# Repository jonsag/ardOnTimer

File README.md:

# ardOnTimer
An on timer with relay, mainly for use in an UV exposure box.  

Time is set with buttons and visualized on an LCD display.  

When setting new time it's saved in eeprom and reloaded at startup.  

Timer range is from 10 seconds to 9 hours, 59 minutes and 59 seconds in 10 seconds steps.  
This can be changed in configuration file.  

Parts list
==========
1 x Arduino Uno, kjell.com art#88860  
1 x LCD display 2x16 characters, kjell.com art# 90215  
1 x Relay module KY-019, kjell.com art# 87878  
1 x Buzzer, kjell.com art# 87887  
4 x Switch, kjell.com art# 36011  
1 x 10kohm potentiometer  
4 x 10kohm resistor  
1 x 220ohm resistor  
1x 100ohm resistor  

Screens
==========
The timer has three screens.  
Second row on screens shows which buttons are active.  

Standby screen
----------
Waiting for start or set.  

 * Start/Stop/Store button to start timer and enter run screen.  
 * Set button to enter set screen.  

Run screen
----------
Shows spinning bar and time left on first row, and progressbar on the second.  

 * Start/Stop/Store button to stop timer and go back to standby screen.  

Set screen
----------
Setting timer.  

* Start/Stop/Store button to store set time.  
* Set button to exit back to standby screen. If set time was not stored, previous time will be used.  
* Up or Down button to increase/decrease time. Each press adds/subtracts 10 seconds from time. Long press adds/subtracts one minute from time. Holding down button keeps stepping minutes.

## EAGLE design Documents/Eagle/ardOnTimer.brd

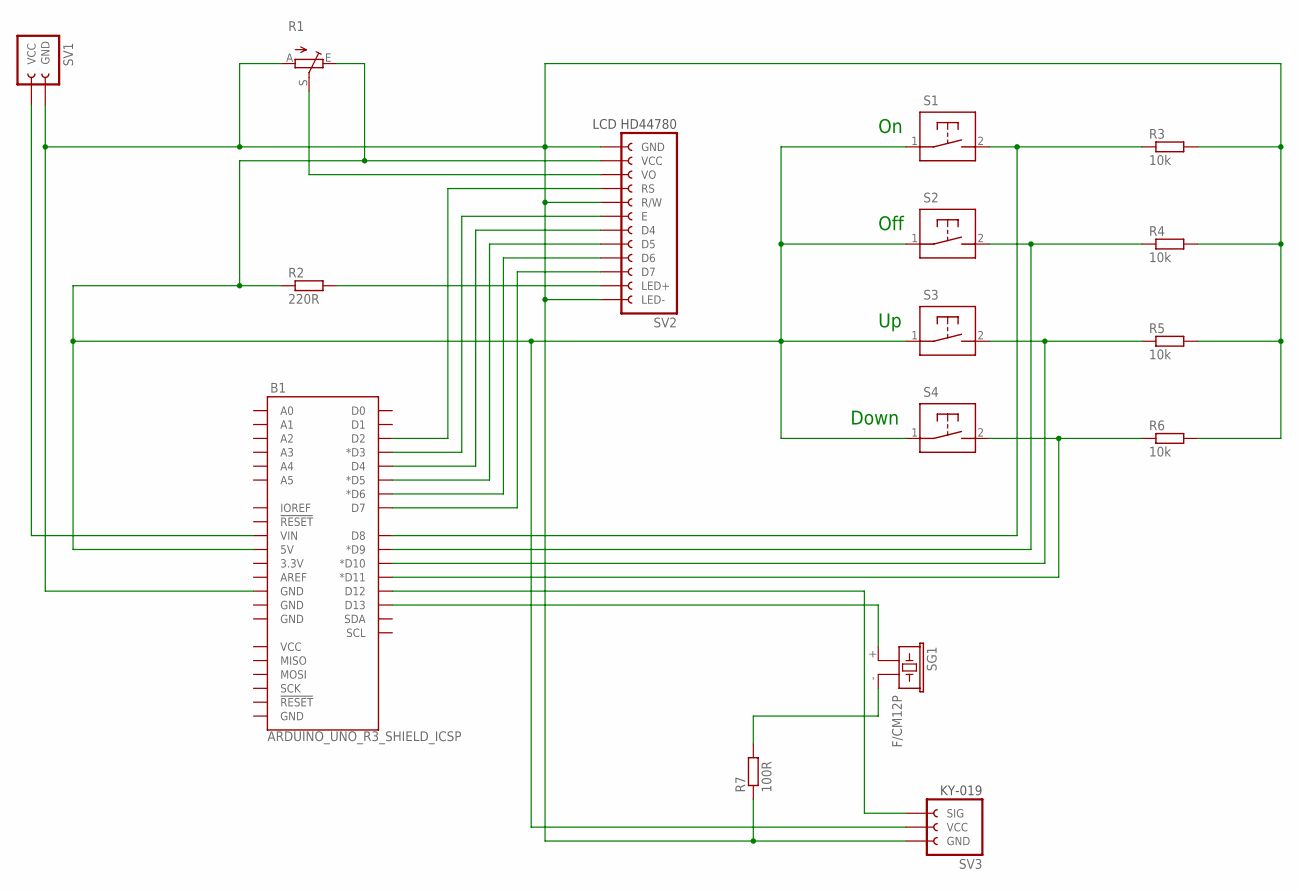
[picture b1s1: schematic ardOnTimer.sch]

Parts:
B1: ARDUINO_UNO_R3_SHIELD_ICSP; UNO_R3_SHIELD_ICSP
R1: POTENTIOMETER_CA6VCA6V; CA6V
R2: 220R; 0204/7
R3, R4, R5, R6: 10k; 0204/7
R7: 100R; 0204/7
S1, S2, S3, S4: NO_SWITCH_2-PIN-FEMALE_HEADER
SG1: F/CM12P
SV1: POWER_IN-2-PIN_FEMALE_HEADER
SV2: LCD-HD44780-12-PIN_FEMALE_HEADER
SV3: KY-019_3-PIN_FEMALE_HEADERANGLED_W_MOUNT_HOLES; KY-019_3-PIN_FEMALE_HEADER_ANGLED_W_MOUNT_HOLES

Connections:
unnamed: B1.GND@2 (GND), R1.A, R3.2, R4.2, R5.2, R6.2, R7.1, SV1.GND, SV2.GND, SV2.LED-, SV2.R/W, SV3.GND
unnamed: B1.D13, SG1.+ (1)
unnamed: R1.S, SV2.VO
unnamed: R2.2, SV2.LED+
unnamed: B1.D2, SV2.RS
unnamed: B1.D3 (*D3), SV2.E
unnamed: B1.D4, SV2.D4
unnamed: B1.D5 (*D5), SV2.D5
unnamed: B1.D6 (*D6), SV2.D6
unnamed: B1.D7, SV2.D7
unnamed: B1.VIN, SV1.VCC
unnamed: B1.5V, R1.E, R2.1, S1.1, S2.1, S3.1, S4.1, SV2.VCC, SV3.VCC
unnamed: B1.D8, R3.1, S1.2 (S)
unnamed: B1.D9 (*D9), R4.1, S2.2 (S)
unnamed: B1.D10 (*D10), R5.1, S3.2 (S)
unnamed: B1.D11 (*D11), R6.1, S4.2 (S)
unnamed: B1.D12, SV3.SIG
unnamed: R7.2, SG1.- (2)

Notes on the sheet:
Off
Down

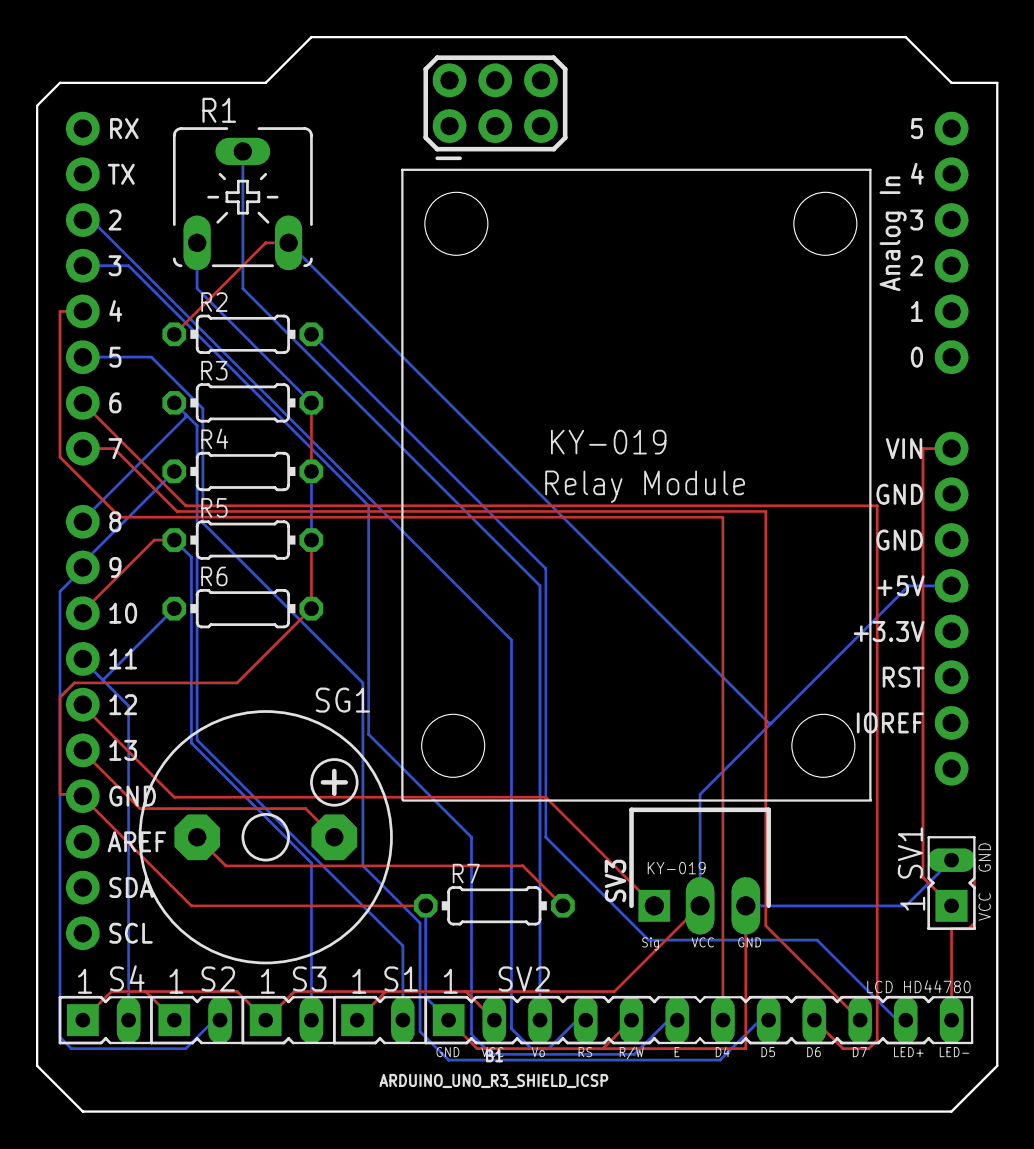
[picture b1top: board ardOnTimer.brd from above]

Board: 2 copper layers, 53.3 x 59.7 mm, 16 parts (0 on the bottom side), 18 nets.

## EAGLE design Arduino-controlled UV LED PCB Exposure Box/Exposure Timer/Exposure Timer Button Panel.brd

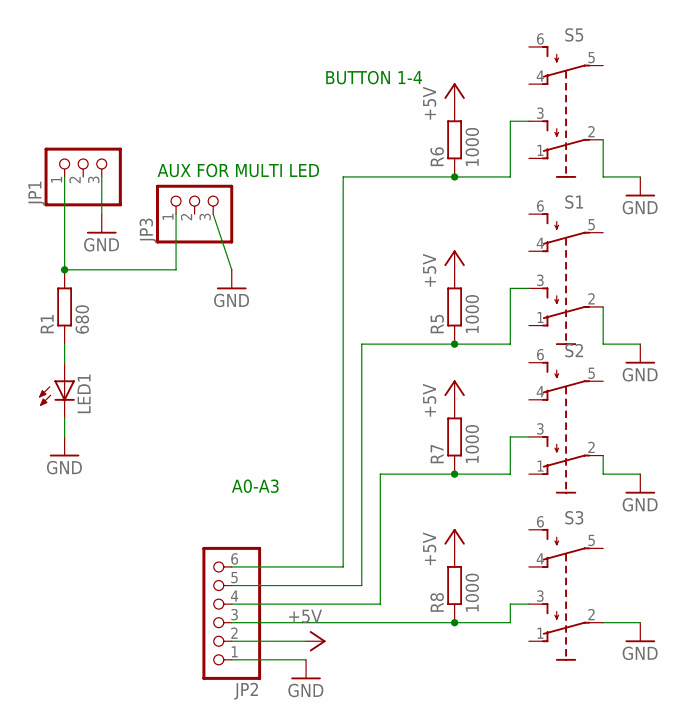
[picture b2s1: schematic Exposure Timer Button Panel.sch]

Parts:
JP1, JP3: PINHD-1X3; 1X03
JP2: PINHD-1X6; 1X06
LED1: LED5MM
R1: 680; 0204/7
R5, R6, R7, R8: 1000; 0204/7
S1, S2, S3, S5: TL42PO; TL4XPO

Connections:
+5V: JP2.2, R5.2, R6.2, R7.2, R8.2
GND: JP1.3, JP2.1, JP3.3, LED1.K (C), S1.2, S2.2, S3.2, S5.2
unnamed: JP1.1, JP3.1, R1.2
unnamed: LED1.A, R1.1
unnamed: JP2.6, R6.1, S5.3 (S)
unnamed: JP2.5, R5.1, S1.3 (S)
unnamed: JP2.4, R7.1, S2.3 (S)
unnamed: JP2.3, R8.1, S3.3 (S)

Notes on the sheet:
BUTTON 1-4
A0-A3
AUX FOR MULTI LED

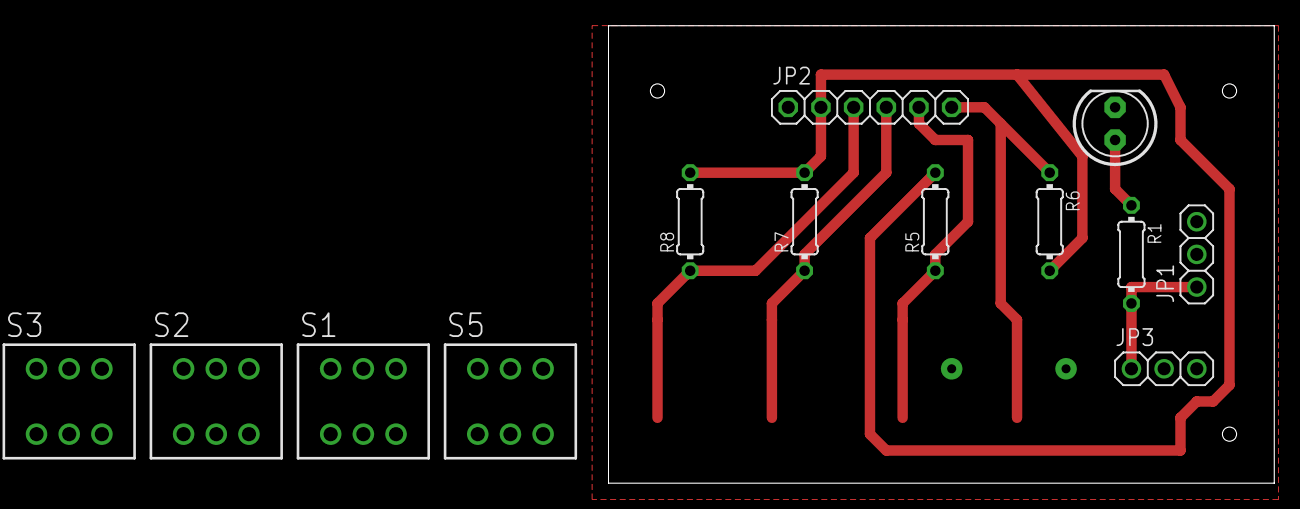
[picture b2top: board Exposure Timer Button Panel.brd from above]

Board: 2 copper layers, 51.7 x 35.5 mm, 13 parts (0 on the bottom side), 8 nets.

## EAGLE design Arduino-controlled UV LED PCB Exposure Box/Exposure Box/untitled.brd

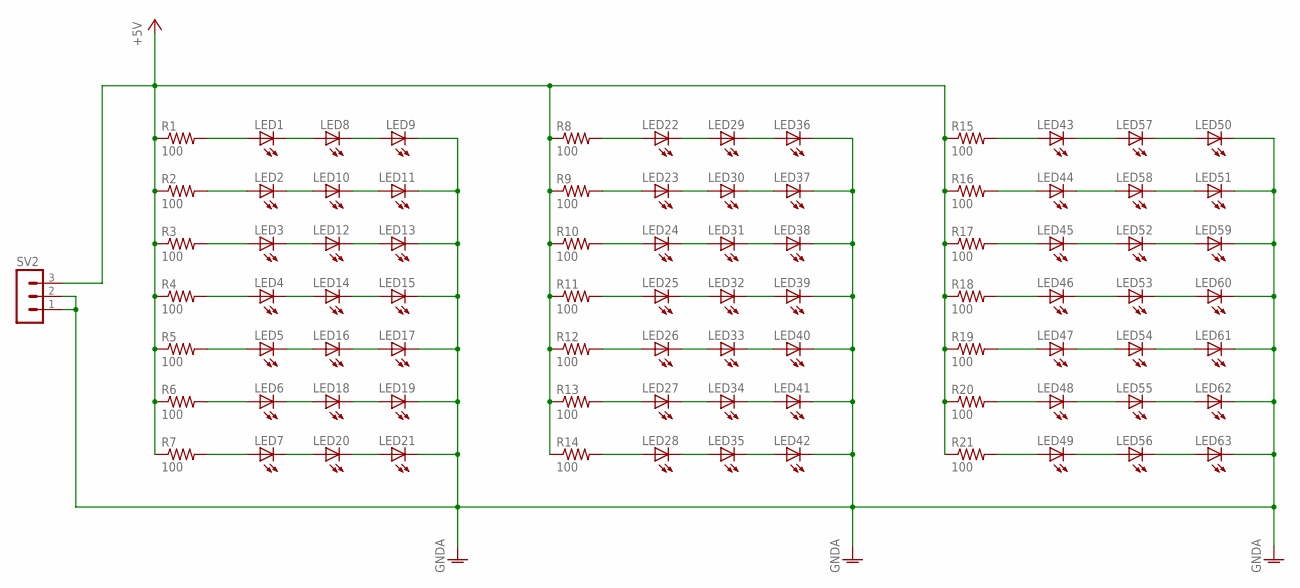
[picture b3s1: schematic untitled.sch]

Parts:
LED1, LED2, LED3, LED4, LED5, LED6, LED7, LED8, LED9, LED10, LED11, LED12, LED13, LED14, LED15, LED16, LED17, LED18, LED19, LED20, LED21, LED22, LED23, LED24, LED25, LED26, LED27, LED28, LED29, LED30, LED31, LED32, LED33, LED34, LED35, LED36, LED37, LED38, LED39, LED40, LED41, LED42, LED43, LED44, LED45, LED46, LED47, LED48, LED49, LED50, LED51, LED52, LED53, LED54, LED55, LED56, LED57, LED58, LED59, LED60, LED61, LED62, LED63: LED5MM
R1, R2, R3, R4, R5, R6, R7, R8, R9, R10, R11, R12, R13, R14, R15, R16, R17, R18, R19, R20, R21: 100; 0204/5
SV2: MA03-1

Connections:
+5V: R1.1, R2.1, R3.1, R4.1, R5.1, R6.1, R7.1, R8.1, R9.1, R10.1, R11.1, R12.1, R13.1, R14.1, R15.1, R16.1, R17.1, R18.1, R19.1, R20.1, R21.1, SV2.3
GNDA: LED9.K (C), LED11.K (C), LED13.K (C), LED15.K (C), LED17.K (C), LED19.K (C), LED21.K (C), LED36.K (C), LED37.K (C), LED38.K (C), LED39.K (C), LED40.K (C), LED41.K (C), LED42.K (C), LED50.K (C), LED51.K (C), LED59.K (C), LED60.K (C), LED61.K (C), LED62.K (C), LED63.K (C), SV2.1, SV2.2
unnamed: LED43.K (C), LED57.A
unnamed: LED52.K (C), LED59.A
unnamed: LED1.A, R1.2
unnamed: LED2.A, R2.2
unnamed: LED3.A, R3.2
unnamed: LED4.A, R4.2
unnamed: LED5.A, R5.2
unnamed: LED6.A, R6.2
unnamed: LED7.A, R7.2
unnamed: LED53.K (C), LED60.A
unnamed: LED1.K (C), LED8.A
unnamed: LED8.K (C), LED9.A
unnamed: LED10.K (C), LED11.A
unnamed: LED2.K (C), LED10.A
unnamed: LED3.K (C), LED12.A
unnamed: LED12.K (C), LED13.A
unnamed: LED54.K (C), LED61.A
unnamed: LED4.K (C), LED14.A
unnamed: LED14.K (C), LED15.A
unnamed: LED16.K (C), LED17.A
unnamed: LED5.K (C), LED16.A
unnamed: LED6.K (C), LED18.A
unnamed: LED18.K (C), LED19.A
unnamed: LED20.K (C), LED21.A
unnamed: LED7.K (C), LED20.A
unnamed: LED55.K (C), LED62.A
unnamed: LED56.K (C), LED63.A
unnamed: LED22.A, R8.2
unnamed: LED23.A, R9.2
unnamed: LED24.A, R10.2
unnamed: LED25.A, R11.2
unnamed: LED26.A, R12.2
unnamed: LED27.A, R13.2
unnamed: LED28.A, R14.2
unnamed: LED22.K (C), LED29.A
unnamed: LED29.K (C), LED36.A
unnamed: LED30.K (C), LED37.A
unnamed: LED23.K (C), LED30.A
unnamed: LED24.K (C), LED31.A
unnamed: LED31.K (C), LED38.A
unnamed: LED32.K (C), LED39.A
unnamed: LED25.K (C), LED32.A
unnamed: LED26.K (C), LED33.A
unnamed: LED27.K (C), LED34.A
unnamed: LED28.K (C), LED35.A
unnamed: LED33.K (C), LED40.A
unnamed: LED34.K (C), LED41.A
unnamed: LED35.K (C), LED42.A
unnamed: LED50.A, LED57.K (C)
unnamed: LED51.A, LED58.K (C)
unnamed: LED44.K (C), LED58.A
unnamed: LED43.A, R15.2
unnamed: LED44.A, R16.2
unnamed: LED45.A, R17.2
unnamed: LED46.A, R18.2
unnamed: LED47.A, R19.2
unnamed: LED48.A, R20.2
unnamed: LED49.A, R21.2
unnamed: LED45.K (C), LED52.A
unnamed: LED46.K (C), LED53.A
unnamed: LED47.K (C), LED54.A
unnamed: LED48.K (C), LED55.A
unnamed: LED49.K (C), LED56.A

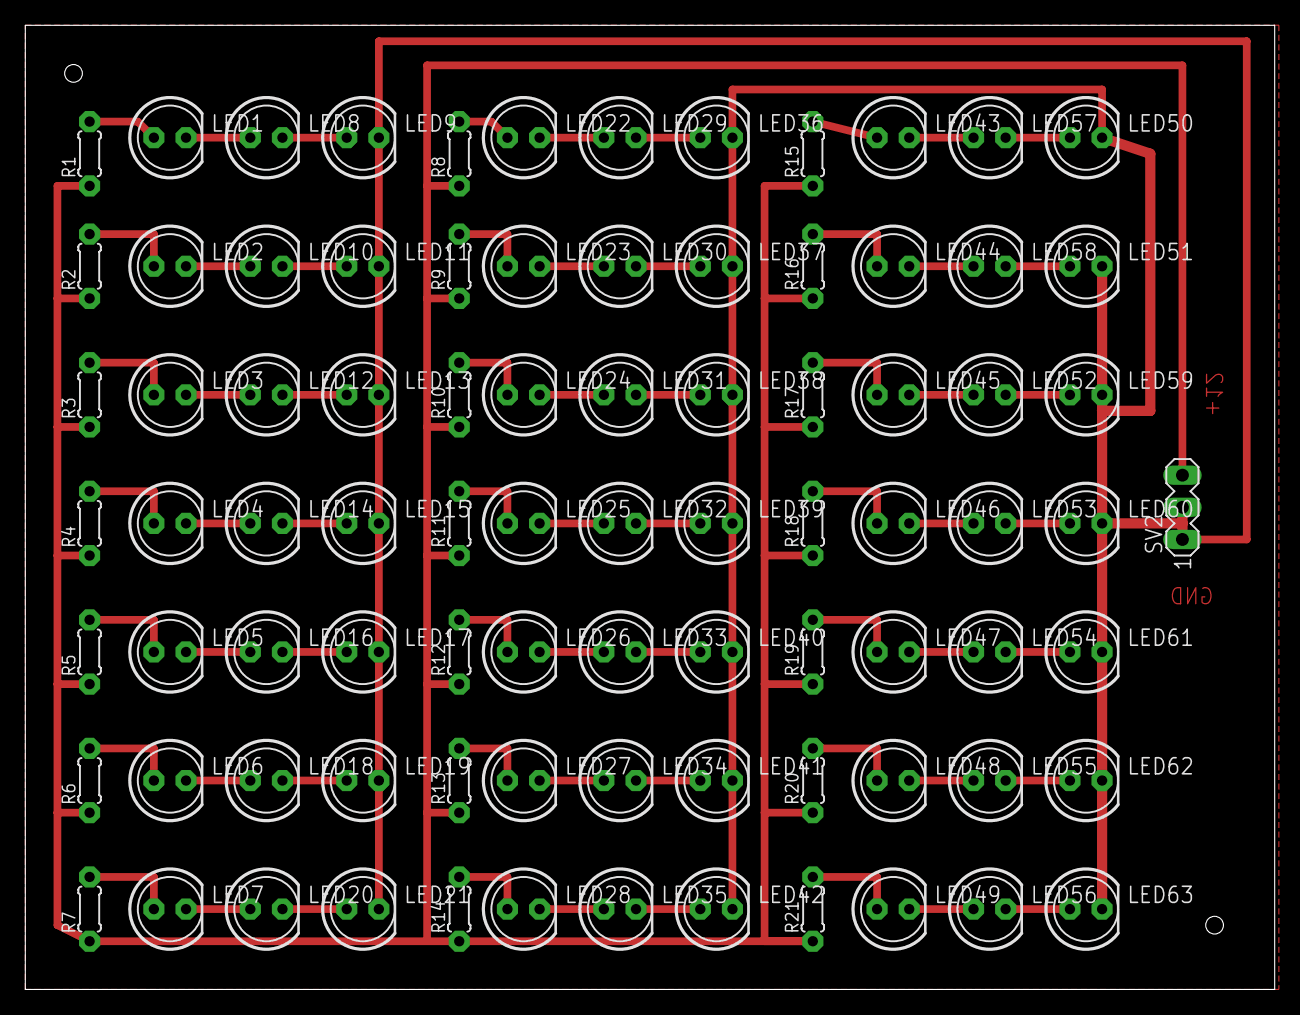
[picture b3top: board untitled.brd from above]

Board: 2 copper layers, 98.7 x 76.2 mm, 85 parts (0 on the bottom side), 65 nets.

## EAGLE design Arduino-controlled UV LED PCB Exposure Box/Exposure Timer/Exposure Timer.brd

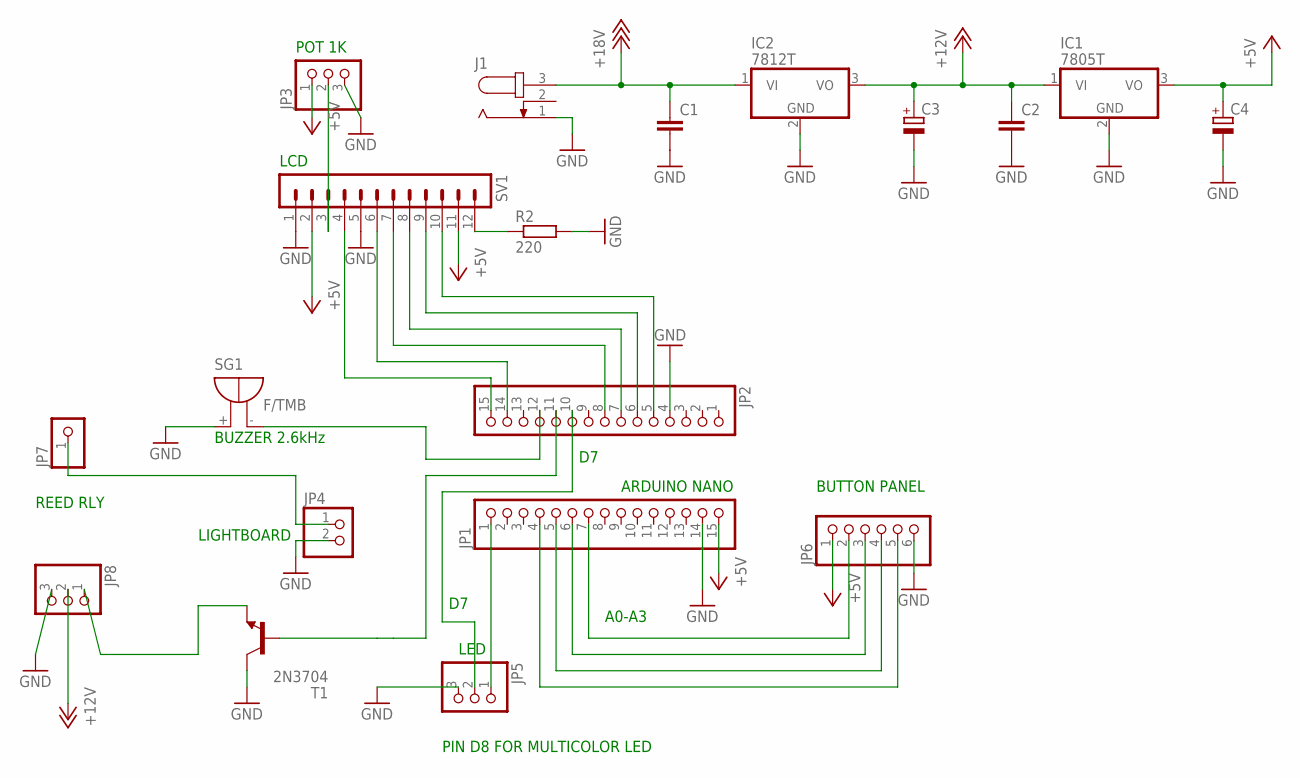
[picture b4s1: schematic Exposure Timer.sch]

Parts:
C1, C2: C-EU025-030X050; C025-030X050
C3, C4: CPOL-EUE2,5-6E; E2,5-6E
IC1: 7805T; TO220H
IC2: 7812T; TO220H
J1: JACK-PLUG1; SPC4078
JP1, JP2: PINHD-1X15; 1X15
JP3, JP5, JP8: PINHD-1X3; 1X03
JP4: PINHD-1X2; 1X02
JP6: PINHD-1X6; 1X06
JP7: PINHD-1X1; 1X01
R2: 220; 0204/7
SG1: F/TMB
SV1: MA12-1
T1: 2N3704; TO92

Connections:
+5V: C4.+, IC1.3 (VO), JP1.15, JP3.1, JP6.1, SV1.2, SV1.11
+12V: C2.1, C3.+, IC1.1 (VI), IC2.3 (VO), JP8.2
+18V: C1.1, IC2.1 (VI), J1.3
GND: C1.2, C2.2, C3.-, C4.-, IC1.2 (GND), IC2.2 (GND), J1.1, JP1.14, JP2.4, JP3.3, JP4.2, JP5.3, JP6.6, JP8.3, R2.2, SG1.+, SV1.1, SV1.5, T1.2 (C)
unnamed: R2.1, SV1.12
unnamed: JP2.8, SV1.7
unnamed: JP2.6, SV1.9
unnamed: JP1.1, JP5.1
unnamed: JP2.5, SV1.10
unnamed: JP2.14, SV1.6
unnamed: JP2.15, SV1.4
unnamed: JP2.12, SG1.-
unnamed: JP3.2, SV1.3
unnamed: JP2.10, JP5.2
unnamed: JP2.7, SV1.8
unnamed: JP8.1, T1.3 (E)
unnamed: JP4.1, JP7.1
unnamed: JP1.7, JP6.2
unnamed: JP1.6, JP6.3
unnamed: JP1.5, JP6.4
unnamed: JP1.4, JP6.5
T1: JP2.11, T1.1 (B)

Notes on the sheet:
LIGHTBOARD
LCD
POT 1K
A0-A3
ARDUINO NANO
BUTTON PANEL
LED
PIN D8 FOR MULTICOLOR LED
REED RLY
BUZZER 2.6kHz

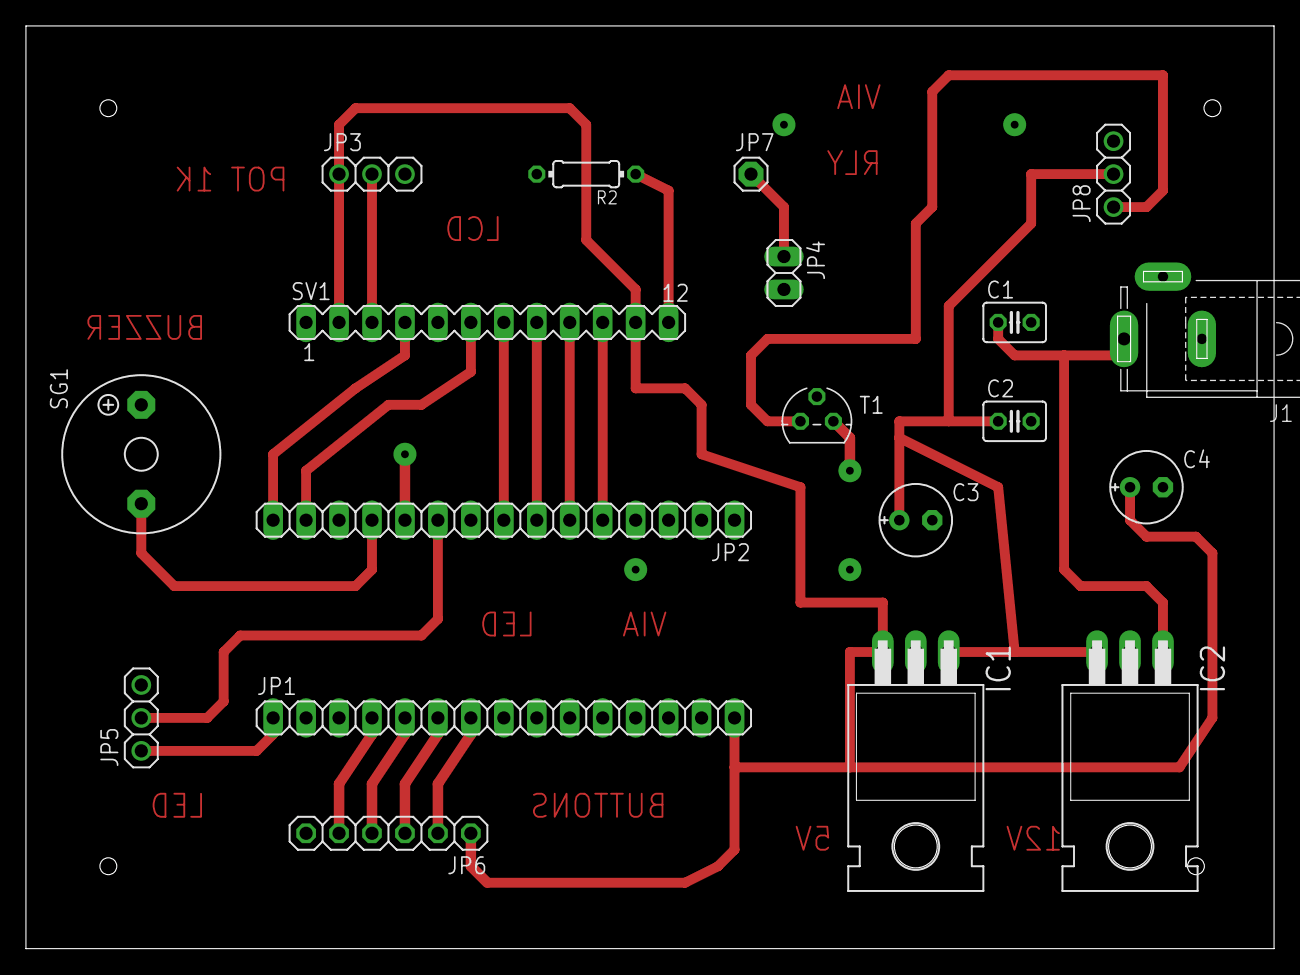
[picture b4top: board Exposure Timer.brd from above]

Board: 2 copper layers, 96.2 x 71.1 mm, 19 parts (0 on the bottom side), 22 nets.

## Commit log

2020-01-26 added example
2020-01-26 deleted files
2020-01-26 added sketch
2020-01-26 split code
2020-01-27 sketch update
2020-01-28 mostly working sketch
2020-01-28 forgot some .h
2020-01-28 added Eagle schematics
2020-01-29 Sketch stores new value in eeprom. Enhanced lcd layout
2020-01-29 Output change. Bugs
2020-01-30 added some experimental code for increasing set speed, not implemented
2020-01-30 now speeds up when holding up/down buttons
2020-01-30 Animates run. Up, down arrows. Fast setting.
2020-01-30 Addded progress bar (not tested yet)
2020-01-30 bugs
2020-01-31 Progressbar working
2020-01-31 Deleted older project
2020-01-31 Switched DI12<->DI13
2020-01-31 deleted unnecessary files
2020-01-31 deleted unnecessary file
2020-01-31 Forgot resistor in schematics. Updated readme.
2022-08-28 kicad schematics
2022-09-09 kicad
2022-10-21 kicad v0.3
